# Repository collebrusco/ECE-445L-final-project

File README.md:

# ECE445L Final Lab
Final project for Spring '24 ECE 445L (1st place winner!)    
Frank Collebrusco, Rocco Perciavalle, Connor Leu, Sajid Bhuiyan      

Remote-controlled drag racing! Players use two controllers to drive the dragsters. The controllers have a throttle and a gear shifter, and the players must time their gear shifts for the optimal power output. The controller software simulates engine operation and the resulting power output. Players are penalized for red-lining, shifting too early or too late. The better driver wins!

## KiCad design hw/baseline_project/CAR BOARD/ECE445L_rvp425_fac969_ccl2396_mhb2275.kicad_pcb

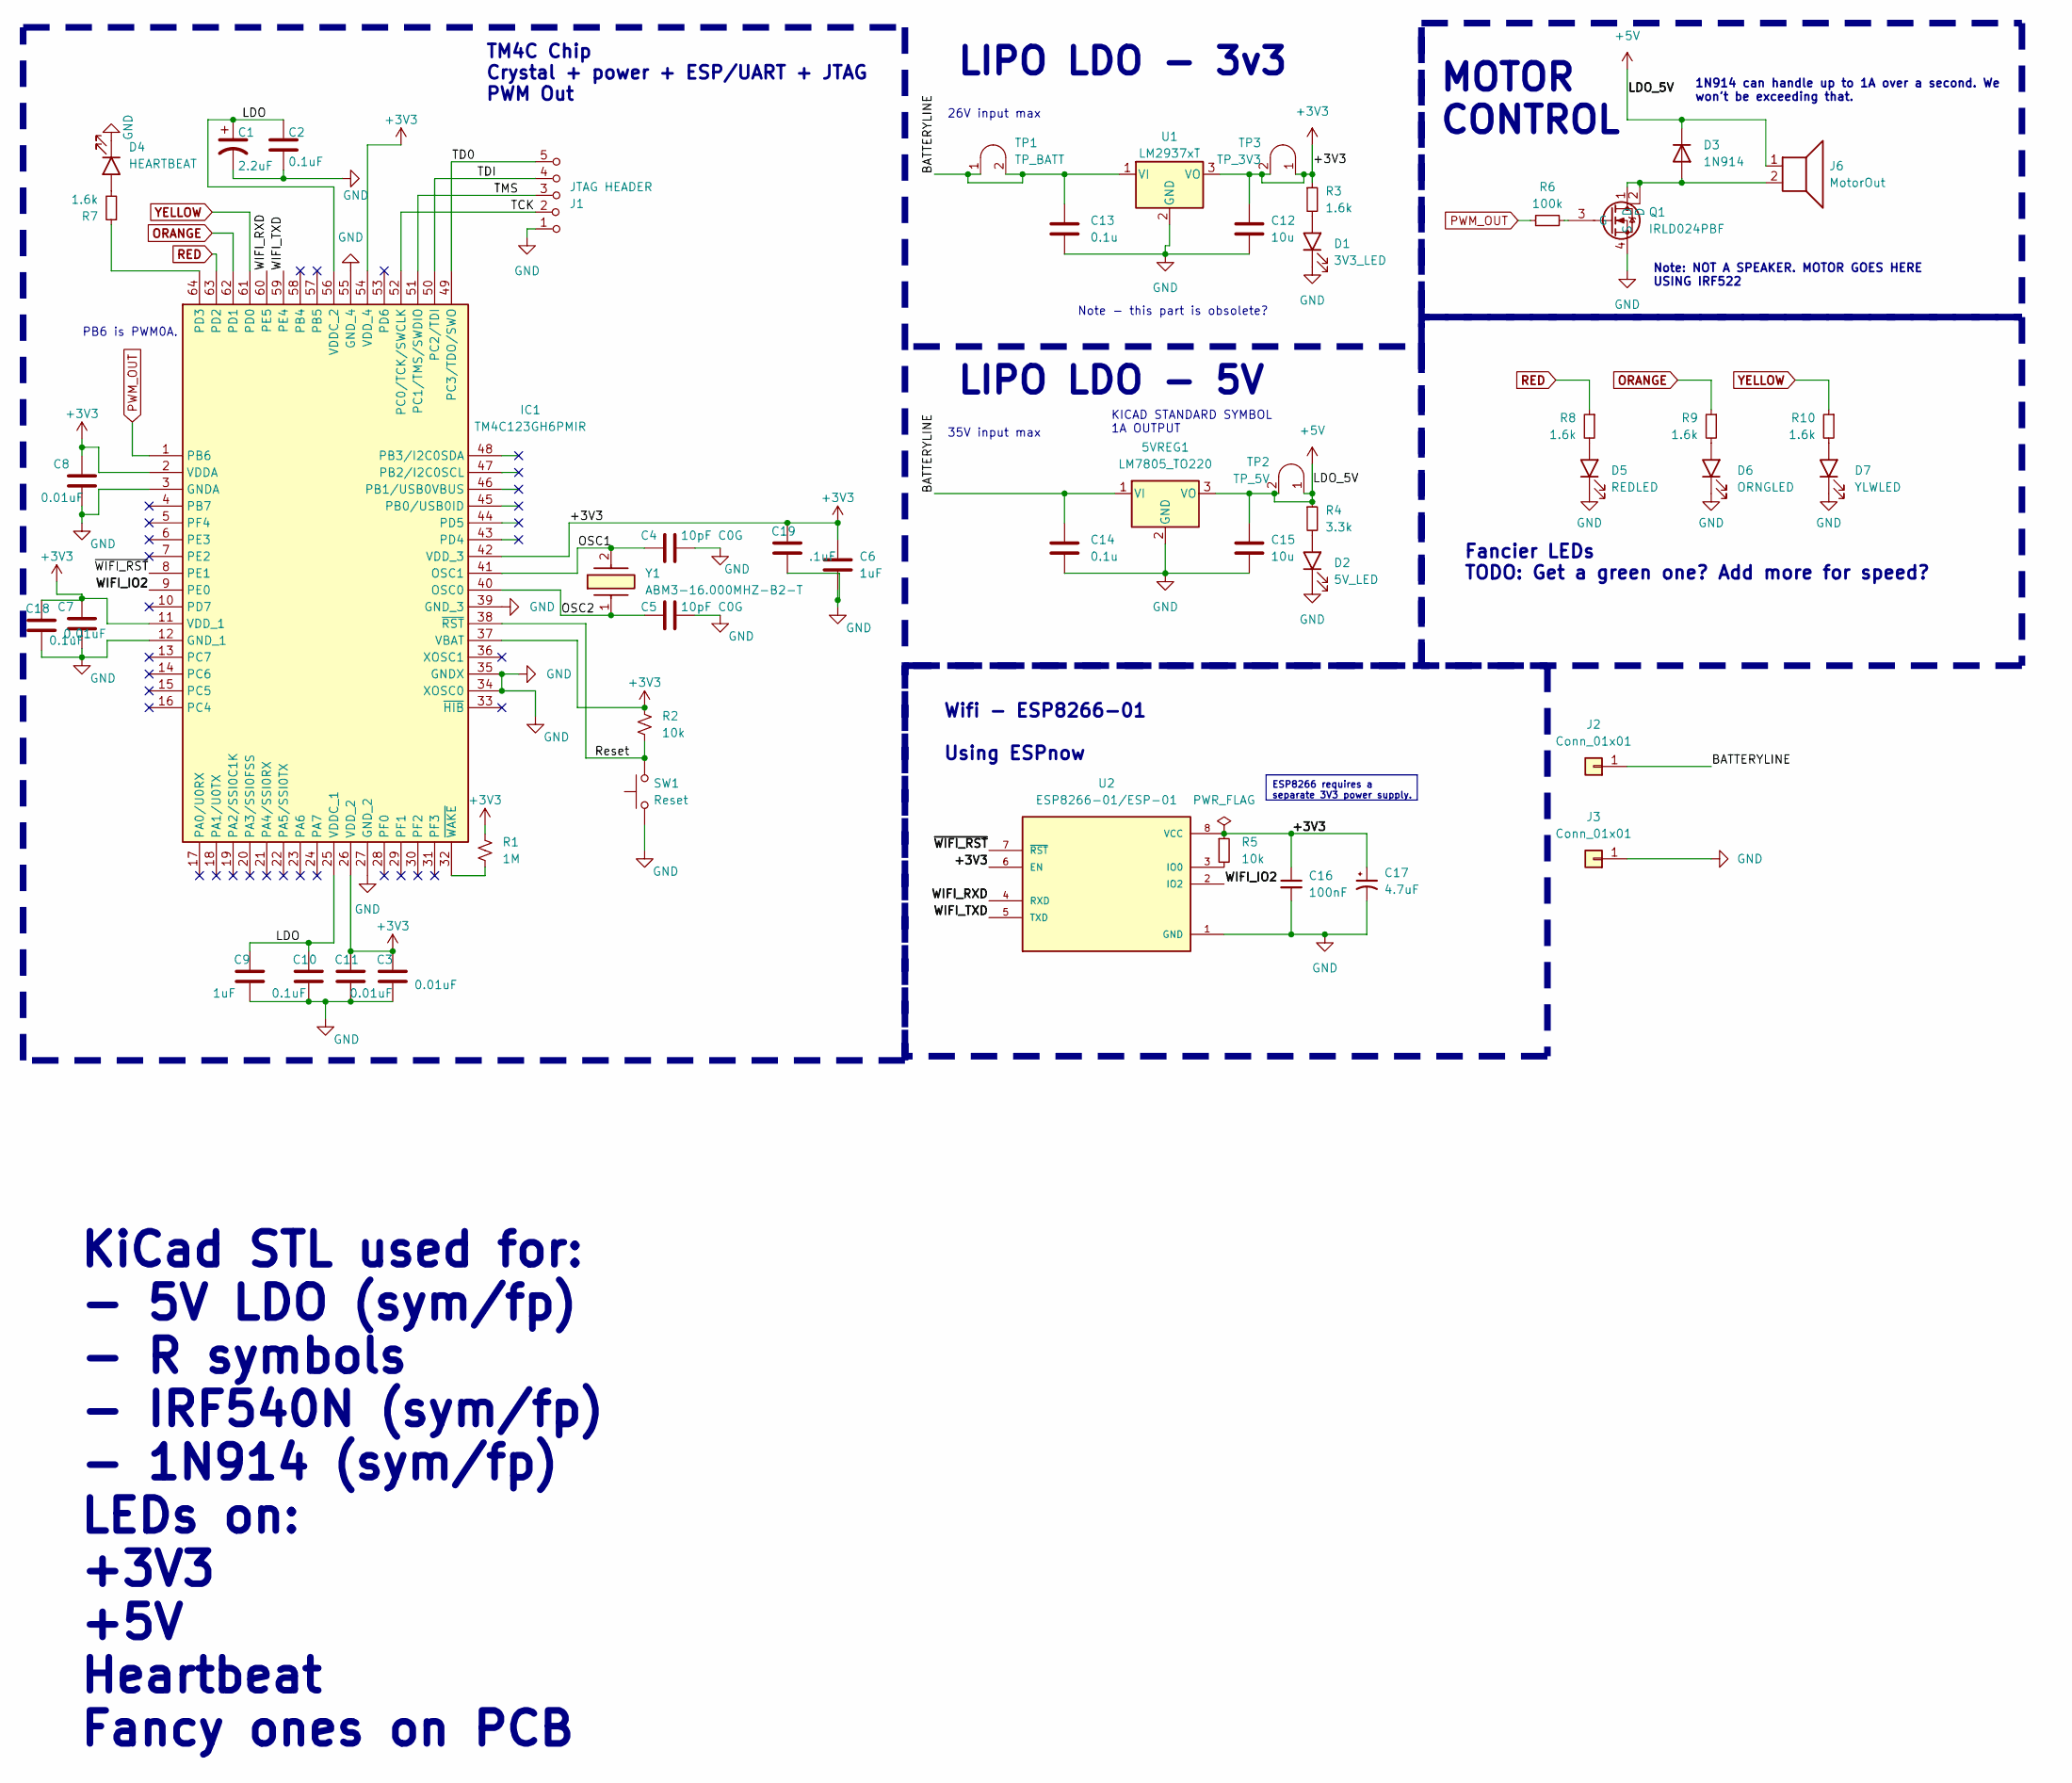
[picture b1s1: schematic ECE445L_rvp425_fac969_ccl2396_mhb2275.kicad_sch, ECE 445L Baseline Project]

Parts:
5VREG1: LM7805_TO220; TO-220-3_Vertical
C1: 2.2uF; CP_Radial_Tantal200mil
C2, C7, C10: 0.1uF; C_Axial_200mil
C3, C8, C11, C18: 0.01uF; C_Axial_200mil
C4, C5: 10pF C0G; C_Axial_200mil
C6, C9: 1uF; C_Axial_200mil
C12, C15: 10u; C_Axial_200mil
C13, C14: 0.1u; C_Axial_200mil
C16: 100nF; C_Axial_L5.1mm_D3.1mm_P15.00mm_Horizontal
C17: 4.7uF; CP_Axial_L10.0mm_D4.5mm_P15.00mm_Horizontal
C19: .1uF; C_Axial_200mil
D1: 3V3_LED; LED_D5.0mm
D2: 5V_LED; LED_D5.0mm
D3: 1N914; D_DO-35_SOD27_P7.62mm_Horizontal
D4: HEARTBEAT; LED_D5.0mm
D5: REDLED; LED_D5.0mm
D6: ORNGLED; LED_D5.0mm
D7: YLWLED; LED_D5.0mm
IC1: TM4C123GH6PMIR; QFP50P1200X1200X160-64N; Mouser Part Number 595-TM4C123GH6PMIR
J1: JTAG HEADER; PinHeader_1x05_P2.54mm_Vertical
J2, J3: Conn_01x01; PinSocket_1x01_P2.54mm_Vertical
J6: MotorOut; PinHeader_1x02_P2.54mm_Vertical
Q1: IRLD024PBF; DIP920W60P254L490H457Q4N; Mouser Part Number 844-IRLD024PBF
R1: 1M; R_Axial_DIN0204_L3.6mm_D1.6mm_P7.62mm_Horizontal
R2, R5: 10k; R_Axial_DIN0204_L3.6mm_D1.6mm_P7.62mm_Horizontal
R3, R7, R8, R9, R10: 1.6k; R_Axial_DIN0204_L3.6mm_D1.6mm_P7.62mm_Horizontal
R4: 3.3k; R_Axial_DIN0204_L3.6mm_D1.6mm_P7.62mm_Horizontal
R6: 100k; R_Axial_DIN0204_L3.6mm_D1.6mm_P7.62mm_Horizontal
SW1: Reset; SW_PUSH_6mm
TP1: TP_BATT; Testpoint_1x02_P2.54mm
TP2: TP_5V; Testpoint_1x02_P2.54mm
TP3: TP_3V3; Testpoint_1x02_P2.54mm
U1: LM2937xT; TO-220-3_Vertical
U2: ESP8266-01/ESP-01; ai_thinker_ESP8266_01
Y1: ABM3-16.000MHZ-B2-T; ABM3; Mouser Part Number 815-ABM3-16-B2-T

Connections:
+3V3: C3.1, C6.1, C7.1, C8.1, C11.1, C12.1, C16.1, C17.1, C18.1, C19.1, IC1.2 (VDDA), IC1.11 (VDD_1), IC1.26 (VDD_2), IC1.37 (VBAT), IC1.42 (VDD_3), IC1.54 (VDD_4), R1.1, R2.1, R3.1, R5.1, TP3.1 (A), TP3.2 (B), U1.3 (VO), U2.6 (EN), U2.8 (VCC)
+5V: 5VREG1.3 (VO), C15.1, D3.1 (K), J6.1, R4.1, TP2.1 (A), TP2.2 (B)
/BATTERYLINE: 5VREG1.1 (VI), C13.1, C14.1, J2.1, TP1.1 (A), TP1.2 (B), U1.1 (VI)
/LDO: C1.1, C2.1, C9.1, C10.1, IC1.25 (VDDC_1), IC1.56 (VDDC_2)
/OSC1: C4.1, IC1.41 (OSC1), Y1.2
/OSC2: C5.1, IC1.40 (OSC0), Y1.1
/Reset: IC1.38 (~RST), R2.2, SW1.2
/TCK: IC1.52 (PC0/TCK/SWCLK), J1.2 (B)
/TD0: IC1.49 (PC3/TDO/SWO), J1.5 (C)
/TDI: IC1.50 (PC2/TDI), J1.4 (C)
/TMS: IC1.51 (PC1/TMS/SWDIO), J1.3 (C)
/WIFI_IO2: IC1.9 (PE0), U2.2 (IO2)
/WIFI_RXD: IC1.60 (PE5), U2.4 (RXD)
/WIFI_TXD: IC1.59 (PE4), U2.5 (TXD)
/~WIFI_RST: IC1.8 (PE1), U2.7 (~RST)
GND: 5VREG1.2 (GND), C1.2, C2.2, C3.2, C4.2, C5.2, C6.2, C7.2, C8.2, C9.2, C10.2, C11.2, C12.2, C13.2, C14.2, C15.2, C16.2, C17.2, C18.2, C19.2, D1.1 (K), D2.1 (K), D4.1 (K), D5.1 (K), D6.1 (K), D7.1 (K), IC1.3 (GNDA), IC1.12 (GND_1), IC1.27 (GND_2), IC1.34 (XOSC0), IC1.35 (GNDX), IC1.39 (GND_3), IC1.55 (GND_4), J1.1 (A), J3.1, Q1.4 (S), SW1.1, U1.2 (GND), U2.1 (GND)
unnamed: D1.2 (A), R3.2
unnamed: D2.2 (A), R4.2
unnamed: D3.2 (A), J6.2, Q1.1 (D), Q1.2 (D)
unnamed: D4.2 (A), R7.2
unnamed: D5.2 (A), R8.2
unnamed: D6.2 (A), R9.2
unnamed: D7.2 (A), R10.2
unnamed: IC1.64 (PD3), R7.1
unnamed: IC1.32 (~WAKE), R1.2
unnamed: Q1.3 (G), R6.2
unnamed: R5.2, U2.3 (IO0)
ORANGE: IC1.62 (PD1), R9.1
PWM_OUT: IC1.1 (PB6), R6.1
RED: IC1.63 (PD2), R8.1
YELLOW: IC1.61 (PD0), R10.1

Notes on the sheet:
ESP8266 requires a separate 3V3 power supply.
Note - this part is obsolete?
35V input max
KICAD STANDARD SYMBOL 1A OUTPUT
TM4C Chip Crystal + power + ESP/UART + JTAG PWM Out
Fancier LEDs TODO: Get a green one? Add more for speed?
1N914 can handle up to 1A over a second. We won't be exceeding that.
LIPO LDO - 5V
KiCad STL used for: - 5V LDO (sym/fp) - R symbols - IRF540N (sym/fp) - 1N914 (sym/fp) LEDs on: +3V3 +5V Heartbeat Fancy ones on PCB
MOTOR CONTROL
Wifi - ESP8266-01 Using ESPnow
26V input max
LIPO LDO - 3v3
Note: NOT A SPEAKER. MOTOR GOES HERE USING IRF522
PB6 is PWM0A.

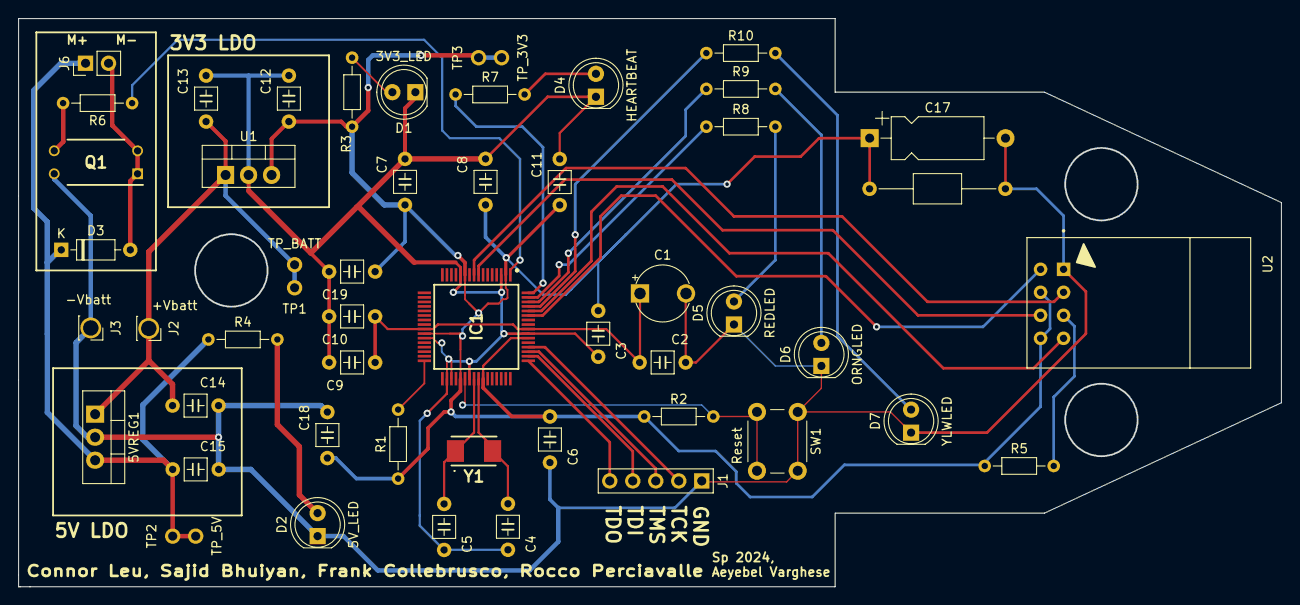
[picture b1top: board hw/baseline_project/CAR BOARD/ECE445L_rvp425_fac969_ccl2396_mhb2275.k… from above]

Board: 2 copper layers, 139.3 x 62.6 mm, 50 parts (0 on the bottom side), 31 nets.

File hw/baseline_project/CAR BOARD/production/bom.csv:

Designator,Footprint,Quantity,Value,LCSC Part #
5VREG1,TO-220-3_Vertical,1,LM7805_TO220,
C1,CP_Radial_Tantal200mil,1,2.2uF,
"C10, C2, C7",C_Axial_200mil,3,0.1uF,
"C11, C18, C3, C8",C_Axial_200mil,4,0.01uF,
"C12, C15",C_Axial_200mil,2,10u,
"C13, C14",C_Axial_200mil,2,0.1u,
C16,C_Axial_L5.1mm_D3.1mm_P15.00mm_Horizontal,1,100nF,
C17,CP_Axial_L10.0mm_D4.5mm_P15.00mm_Horizontal,1,4.7uF,
C19,C_Axial_200mil,1,.1uF,
"C4, C5",C_Axial_200mil,2,10pF C0G,
"C6, C9",C_Axial_200mil,2,1uF,
D1,LED_D5.0mm,1,3V3_LED,
D2,LED_D5.0mm,1,5V_LED,
D3,D_DO-35_SOD27_P7.62mm_Horizontal,1,1N914,
D4,LED_D5.0mm,1,HEARTBEAT,
D5,LED_D5.0mm,1,REDLED,
D6,LED_D5.0mm,1,ORNGLED,
D7,LED_D5.0mm,1,YLWLED,
IC1,QFP50P1200X1200X160-64N,1,TM4C123GH6PMIR,
J1,PinHeader_1x05_P2.54mm_Vertical,1,JTAG HEADER,
"J2, J3",PinSocket_1x01_P2.54mm_Vertical,2,Conn_01x01,
J6,PinHeader_1x02_P2.54mm_Vertical,1,MotorOut,
Q1,DIP920W60P254L490H457Q4N,1,IRLD024PBF,
R1,R_Axial_DIN0204_L3.6mm_D1.6mm_P7.62mm_Horizontal,1,1M,
"R10, R3, R7, R8, R9",R_Axial_DIN0204_L3.6mm_D1.6mm_P7.62mm_Horizontal,5,1.6k,
"R2, R5",R_Axial_DIN0204_L3.6mm_D1.6mm_P7.62mm_Horizontal,2,10k,
R4,R_Axial_DIN0204_L3.6mm_D1.6mm_P7.62mm_Horizontal,1,3.3k,
R6,R_Axial_DIN0204_L3.6mm_D1.6mm_P7.62mm_Horizontal,1,100k,
SW1,SW_PUSH_6mm,1,Reset,
TP1,Testpoint_1x02_P2.54mm,1,TP_BATT,
TP2,Testpoint_1x02_P2.54mm,1,TP_5V,
TP3,Testpoint_1x02_P2.54mm,1,TP_3V3,
U1,TO-220-3_Vertical,1,LM2937xT,
U2,ai_thinker_ESP8266_01,1,ESP8266-01/ESP-01,
Y1,ABM3,1,ABM3-16.000MHZ-B2-T,

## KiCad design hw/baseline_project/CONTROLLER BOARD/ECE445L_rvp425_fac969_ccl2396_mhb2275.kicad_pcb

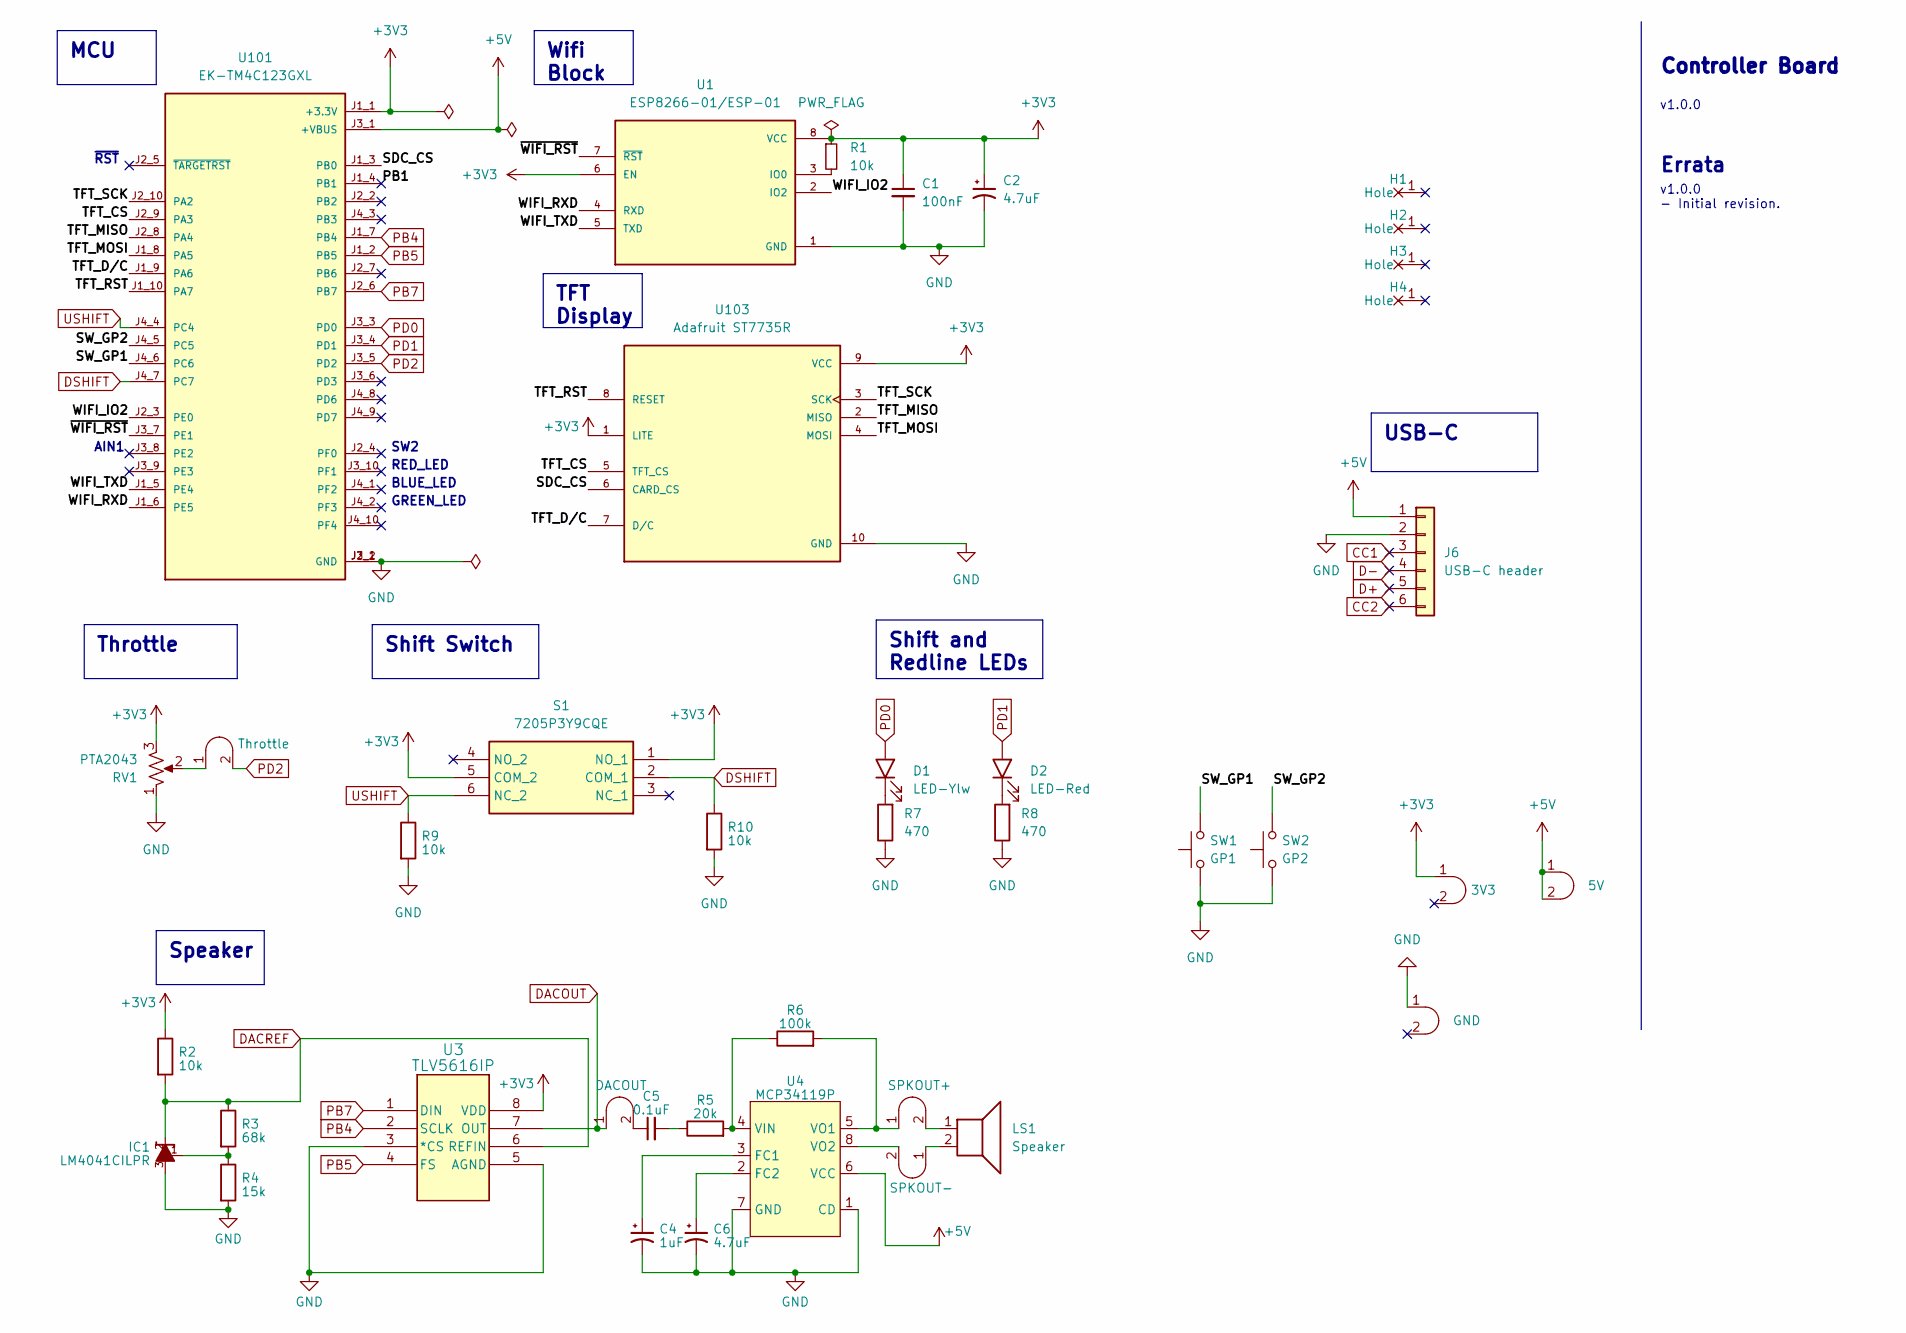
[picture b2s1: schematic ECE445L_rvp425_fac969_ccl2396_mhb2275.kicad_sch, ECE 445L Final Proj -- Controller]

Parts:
C1: 100nF; C_Axial_200mil
C2, C6: 4.7uF; C_Axial_200mil
C4: 1uF; C_Axial_200mil
C5: 0.1uF; C_Axial_200mil
D1: LED-Ylw; LED_D5.0mm
D2: LED-Red; LED_D5.0mm
H1, H2, H3, H4: MountingHole_4_40
IC1: LM4041CILPR; ti_LM4041CILPR
J1: Throttle; Testpoint_1x02_P2.54mm
J2: DACOUT; Testpoint_1x02_P2.54mm
J3: SPKOUT+; Testpoint_1x02_P2.54mm
J4: SPKOUT-; Testpoint_1x02_P2.54mm
J5: GND; Testpoint_1x02_P2.54mm
J6: USB-C header; PinHeader_1x06_P2.54mm_Vertical
J7: 3V3; Testpoint_1x02_P2.54mm
J8: 5V; Testpoint_1x02_P2.54mm
LS1: Speaker; PinHeader_1x02_P2.54mm_Vertical
R1, R2, R9, R10: 10k; R_Axial_DIN0204_L3.6mm_D1.6mm_P7.62mm_Horizontal
R3: 68k; R_Axial_DIN0204_L3.6mm_D1.6mm_P7.62mm_Horizontal
R4: 15k; R_Axial_DIN0204_L3.6mm_D1.6mm_P7.62mm_Horizontal
R5: 20k; R_Axial_DIN0204_L3.6mm_D1.6mm_P7.62mm_Horizontal
R6: 100k; R_Axial_DIN0204_L3.6mm_D1.6mm_P7.62mm_Horizontal
R7, R8: 470; R_Axial_DIN0204_L3.6mm_D1.6mm_P7.62mm_Horizontal
RV1: PTA2043; PTA2043pot
S1: 7205P3Y9CQE; Manufacturer_Part_Number 7205P3Y9CQE; Mouser Part Number 611-7205P3Y9CQE
SW1: GP1; Testpoint_1x02_P2.54mm
SW2: GP2; Testpoint_1x02_P2.54mm
U1: ESP8266-01/ESP-01; ai_thinker_ESP8266_01
U3: TLV5616IP; ti_TLV5616
U4: MCP34119P; DIP-8_W7.62mm_LongPads
U101: EK-TM4C123GXL; ti_EKTM4C123GXL
U103: Adafruit ST7735R; adafruit_st7735r

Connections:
+3V3: C1.1, C2.1, J7.1 (A), R1.1, R2.1, RV1.3, S1.1 (NO_1), S1.5 (COM_2), U1.6 (EN), U1.8 (VCC), U3.8 (VDD), U101.J1_1 (+3.3V), U103.1 (LITE), U103.9 (VCC)
+5V: J6.1, J8.1 (A), J8.2 (B), U4.6 (VCC), U101.J3_1 (+VBUS)
/PB1: U101.J1_4 (PB1)
/SDC_CS: U101.J1_3 (PB0), U103.6 (CARD_CS)
/SW_GP1: SW1.2, U101.J4_6 (PC6)
/SW_GP2: SW2.2, U101.J4_5 (PC5)
/TFT_CS: U101.J2_9 (PA3), U103.5 (TFT_CS)
/TFT_D/C: U101.J1_9 (PA6), U103.7 (D/C)
/TFT_MISO: U101.J2_8 (PA4), U103.2 (MISO)
/TFT_MOSI: U101.J1_8 (PA5), U103.4 (MOSI)
/TFT_RST: U101.J1_10 (PA7), U103.8 (RESET)
/TFT_SCK: U101.J2_10 (PA2), U103.3 (SCK)
/WIFI_IO2: U1.2 (IO2), U101.J2_3 (PE0)
/WIFI_RXD: U1.4 (RXD), U101.J1_6 (PE5)
/WIFI_TXD: U1.5 (TXD), U101.J1_5 (PE4)
/~WIFI_RST: U1.7 (~RST), U101.J3_7 (PE1)
CC1: J6.3
CC2: J6.6
D+: J6.5
D-: J6.4
DACOUT: J2.1 (A), U3.7 (OUT)
DACREF: IC1.2, R2.2, R3.1, U3.6 (REFIN)
DSHIFT: R10.1, S1.2 (COM_1), U101.J4_7 (PC7)
GND: C1.2, C2.2, C4.2, C6.2, IC1.3, J5.1 (A), J6.2, R4.2, R7.1, R8.1, R9.2, R10.2, RV1.1, SW1.1, SW2.1, U1.1 (GND), U3.3 (*CS), U3.5 (AGND), U4.1 (CD), U4.7 (GND), U101.J2_1 (GND), U101.J3_2 (GND), U103.10 (GND)
unnamed: C5.2, R5.1
unnamed: D1.1 (K), R7.2
unnamed: D2.1 (K), R8.2
unnamed: IC1.1, R3.2, R4.1
unnamed: J1.1 (A), RV1.2
unnamed: C5.1, J2.2 (B)
unnamed: J3.1 (A), R6.2, U4.5 (VO1)
unnamed: J3.2 (B), LS1.1
unnamed: J4.1 (A), LS1.2
unnamed: J4.2 (B), U4.8 (VO2)
unnamed: R1.2, U1.3 (IO0)
unnamed: C4.1, U4.3 (FC1)
unnamed: C6.1, U4.2 (FC2)
unnamed: R5.2, R6.1, U4.4 (VIN)
PB4: U3.2 (SCLK), U101.J1_7 (PB4)
PB5: U3.4 (FS), U101.J1_2 (PB5)
PB7: U3.1 (DIN), U101.J2_6 (PB7)
PD0: D1.2 (A), U101.J3_3 (PD0)
PD1: D2.2 (A), U101.J3_4 (PD1)
PD2: J1.2 (B), U101.J3_5 (PD2)
USHIFT: R9.1, S1.6 (NC_2), U101.J4_4 (PC4)

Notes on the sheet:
MCU
Throttle
Wifi Block
Shift Switch
TFT Display
USB-C
Shift and Redline LEDs
Speaker
v1.0.0 - Initial revision.
~{RST}
AIN1
Controller Board
v1.0.0
Errata
BLUE_LED
RED_LED
SW2
GREEN_LED

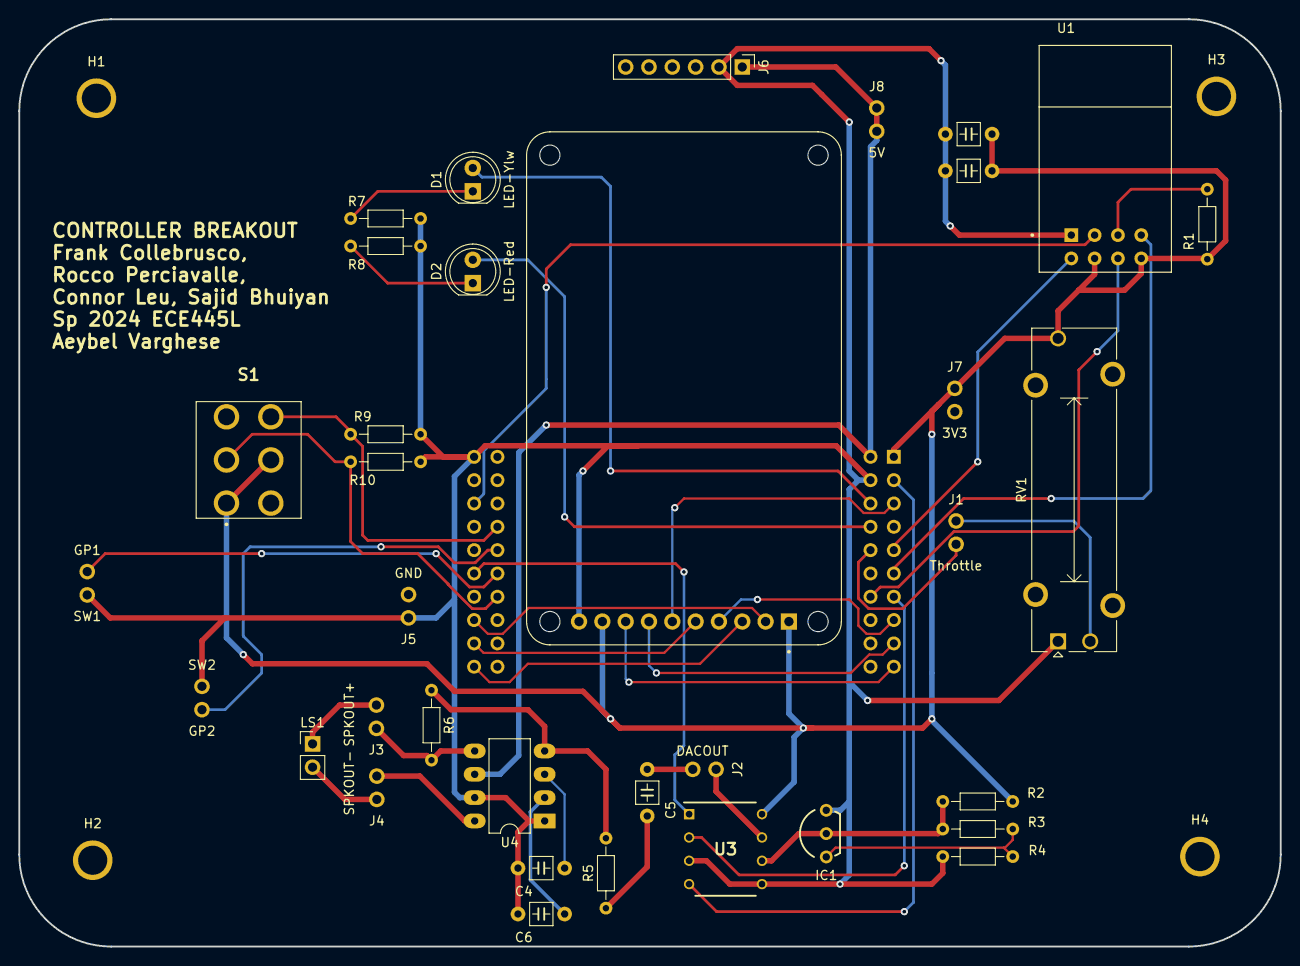
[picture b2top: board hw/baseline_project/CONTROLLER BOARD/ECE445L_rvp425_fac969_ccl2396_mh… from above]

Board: 2 copper layers, 137.4 x 101.0 mm, 40 parts (1 on the bottom side), 40 nets.

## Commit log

2024-05-01 more files
2024-05-01 readme
2024-05-01 readme error
2024-05-01 more readme tweaks
